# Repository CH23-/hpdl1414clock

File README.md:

# hpdl1414clock
A small clock with the HPDL1414 displays (3 of them) and a Pi Pico W running micropython

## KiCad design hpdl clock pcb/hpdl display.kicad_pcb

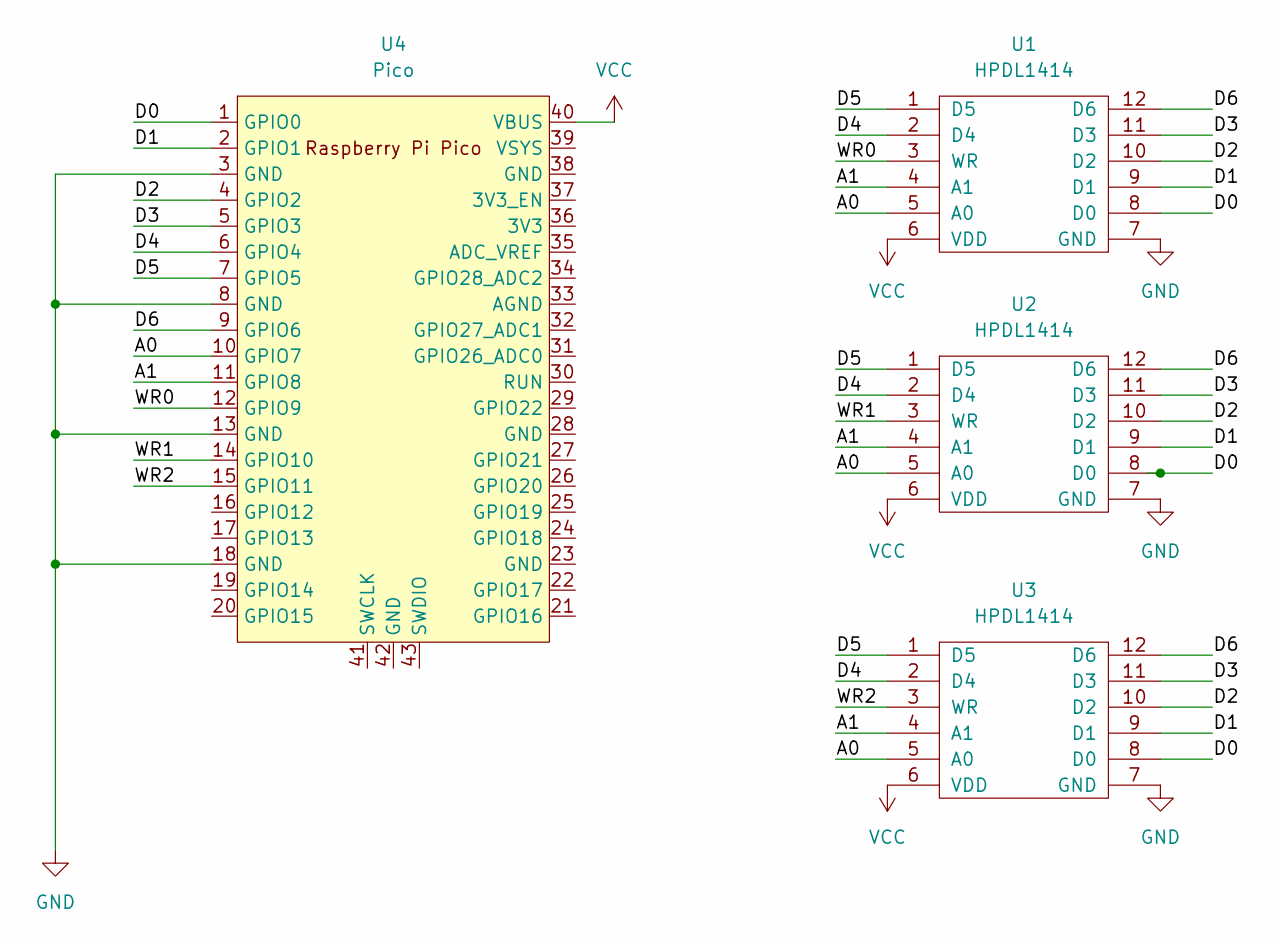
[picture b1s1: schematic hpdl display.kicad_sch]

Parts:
U1, U2, U3: HPDL1414; HPDLDL-1414
U4: Pico; RPi_Pico_SMD_TH

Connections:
/A0: U1.5 (A0), U2.5 (A0), U3.5 (A0), U4.10 (GPIO7)
/A1: U1.4 (A1), U2.4 (A1), U3.4 (A1), U4.11 (GPIO8)
/D0: U1.8 (D0), U2.8 (D0), U3.8 (D0), U4.1 (GPIO0)
/D1: U1.9 (D1), U2.9 (D1), U3.9 (D1), U4.2 (GPIO1)
/D2: U1.10 (D2), U2.10 (D2), U3.10 (D2), U4.4 (GPIO2)
/D3: U1.11 (D3), U2.11 (D3), U3.11 (D3), U4.5 (GPIO3)
/D4: U1.2 (D4), U2.2 (D4), U3.2 (D4), U4.6 (GPIO4)
/D5: U1.1 (D5), U2.1 (D5), U3.1 (D5), U4.7 (GPIO5)
/D6: U1.12 (D6), U2.12 (D6), U3.12 (D6), U4.9 (GPIO6)
/WR0: U1.3 (WR), U4.12 (GPIO9)
/WR1: U2.3 (WR), U4.14 (GPIO10)
/WR2: U3.3 (WR), U4.15 (GPIO11)
GND: U1.7 (GND), U2.7 (GND), U3.7 (GND), U4.3 (GND), U4.8 (GND), U4.13 (GND), U4.18 (GND)
VCC: U1.6 (VDD), U2.6 (VDD), U3.6 (VDD), U4.40 (VBUS)

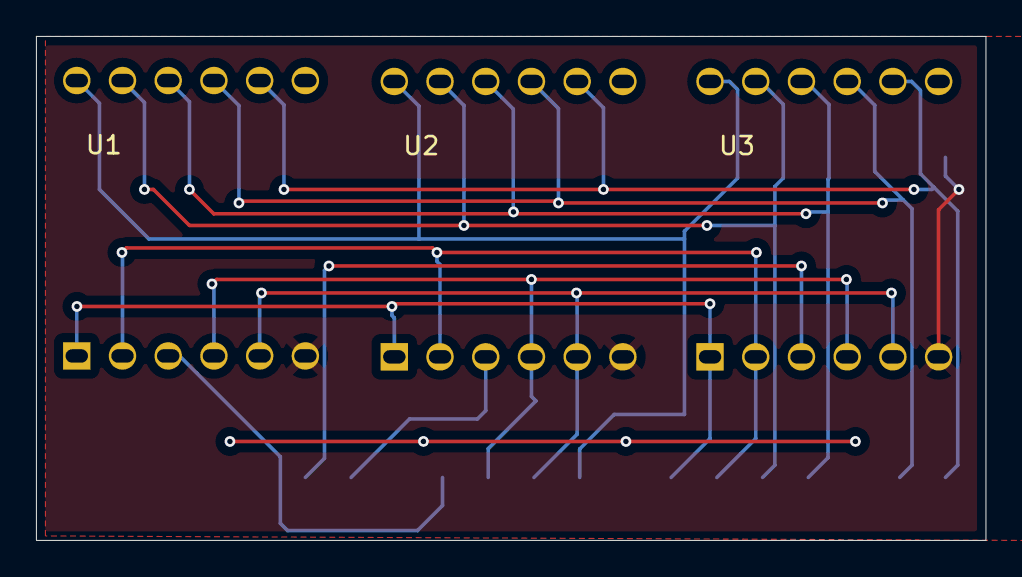
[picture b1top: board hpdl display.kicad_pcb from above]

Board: 2 copper layers, 52.8 x 28.0 mm, 4 parts (1 on the bottom side), 14 nets.

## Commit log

2024-11-10 changed date to yyyy-mm-dd, added switch between date and time
2024-11-14 basically the same script, but for an esp32 c3 super mini. wifi does not yet work
2024-11-14 updated with better wifi code
2025-04-15 Update boot.py
    Now with working wifi and NTP code!
2025-08-15 lots of changes...maybe?
2025-08-16 removed dupplicate code and added miliseconds
